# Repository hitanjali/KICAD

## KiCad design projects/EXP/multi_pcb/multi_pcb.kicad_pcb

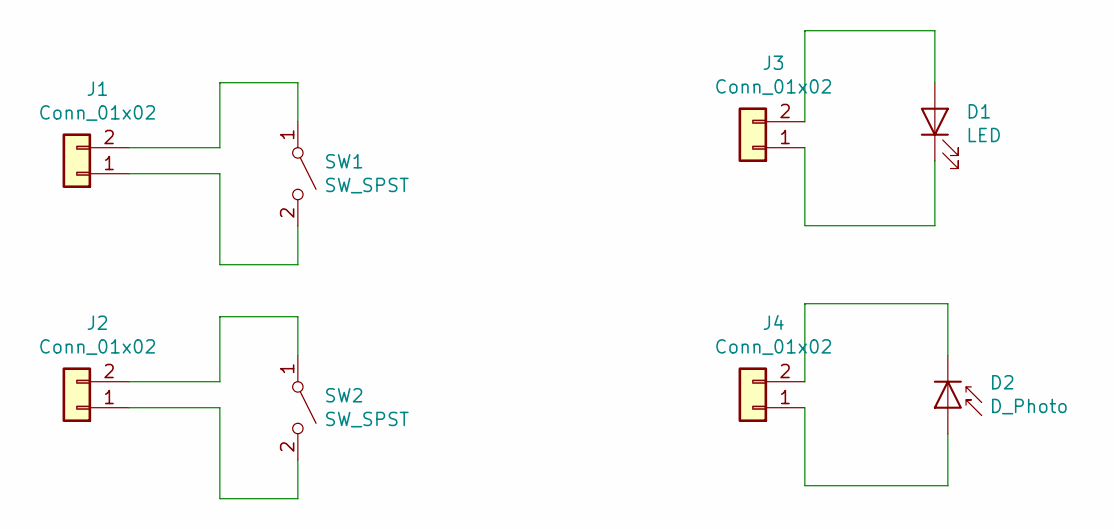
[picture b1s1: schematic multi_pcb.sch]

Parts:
D1: LED; LED_0805_2012Metric
D2: D_Photo; LED_0805_2012Metric
J1, J2, J3, J4: Conn_01x02; JST_EH_B02B-EH-A_1x02_P2.50mm_Vertical
SW1, SW2: SW_SPST; SW_DIP_SPSTx01_Slide_6.7x4.1mm_W6.73mm_P2.54mm_LowProfile_J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

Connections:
unnamed: D1.1 (K), J3.1
unnamed: D1.2 (A), J3.2
unnamed: D2.1 (K), J4.2
unnamed: D2.2 (A), J4.1
unnamed: J1.1, SW1.2 (B)
unnamed: J1.2, SW1.1 (A)
unnamed: J2.1, SW2.2 (B)
unnamed: J2.2, SW2.1 (A)

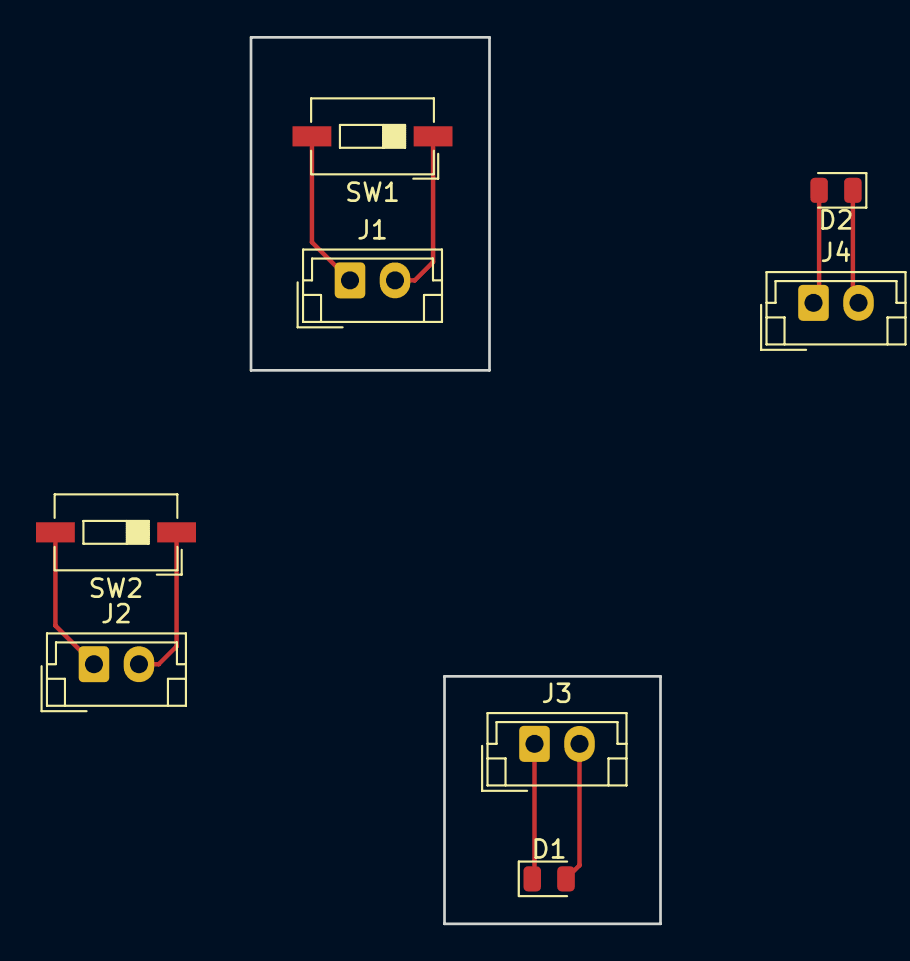
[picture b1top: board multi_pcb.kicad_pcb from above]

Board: 2 copper layers, 8 parts (0 on the bottom side), 8 nets.

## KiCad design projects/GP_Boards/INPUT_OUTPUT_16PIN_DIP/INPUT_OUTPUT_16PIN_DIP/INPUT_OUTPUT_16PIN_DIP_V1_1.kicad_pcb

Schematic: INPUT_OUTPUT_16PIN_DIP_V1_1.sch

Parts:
D1, D2, D3, D4, D5, D6, D7, D8, D9, D10, D11, D12, D13, D14, D15, D16, D17, D18, D19, D20, D21, D22, D23, D24, D25, D26, D27, D28, D29, D30, D31, D32: LED; LED_0603_1608Metric
J1, J2, J7, J8, J9, J12, J22, J28: Conn_01x04; PinHeader_1x04_P2.54mm_Vertical
J3, J6: Conn_01x01; PinHeader_1x01_P2.54mm_Vertical
J4, J5, J11, J24: Conn_02x04_Odd_Even; PinHeader_2x04_P2.54mm_Vertical
J10, J39: Conn_01x08; PinHeader_1x08_P2.54mm_Vertical
J13, J14, J15, J16, J17, J18, J19, J20, J25, J26, J31, J32, J33, J34, J35, J36, J37, J38: Conn_01x03; PinHeader_1x03_P2.54mm_Vertical
J21, J23, J29, J30: Conn_01x02; PinHeader_1x02_P2.54mm_Vertical
J27: Conn_02x08_Counter_Clockwise; DIP-16_W7.62mm
R1, R2, R3, R4, R5, R6, R7, R8, R9, R10, R11, R12, R13, R14, R15, R16, R25, R26, R27, R28, R29, R30, R31, R32, R33, R34, R35, R36, R37, R38, R39, R40: 150; R_1206_3216Metric
R17, R18, R19, R20, R21, R22, R23, R24, R41, R42, R43, R44, R45, R46, R47, R48: 10K; R_1206_3216Metric
RV1, RV2: 20K; Potentiometer_Bourns_3339P_Vertical
SW1, SW2: SW_DIP_x08; DIP-16_W7.62mm

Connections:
/1: J10.1, J13.2, J27.1
/2: J10.2, J14.2, J27.2
/3: J10.3, J15.2, J27.3
/4: J10.4, J16.2, J27.4
/5: J10.5, J17.2, J27.5
/6: J10.6, J18.2, J27.6
/7: J10.7, J19.2, J27.7
/8: J10.8, J20.2, J27.8
/9: J27.9, J31.2, J39.1
/10: J27.10, J32.2, J39.2
/11: J27.11, J33.2, J39.3
/12: J27.12, J34.2, J39.4
/13: J27.13, J35.2, J39.5
/14: J27.14, J36.2, J39.6
/15: J27.15, J37.2, J39.7
/16: J27.16, J38.2, J39.8
/I1: J13.3, R1.2, R17.2, SW1.16
/I2: J14.3, R2.2, R18.2, SW1.15
/I3: J15.3, R3.2, R19.2, SW1.14
/I4: J16.3, R4.2, R20.2, SW1.13
/I5: J17.3, R5.2, R21.2, SW1.12
/I6: J18.3, R6.2, R22.2, SW1.11
/I7: J19.3, R7.2, R23.2, SW1.10
/I8: J20.3, R8.2, R24.2, SW1.9
/I9: J31.1, R40.2, R48.2, SW2.8
/I10: J32.1, R39.2, R47.2, SW2.7
/I11: J33.1, R38.2, R46.2, SW2.6
/I12: J34.1, R37.2, R45.2, SW2.5
/I13: J35.1, R36.2, R44.2, SW2.4
/I14: J36.1, R35.2, R43.2, SW2.3
/I15: J37.1, R34.2, R42.2, SW2.2
/I16: J38.1, R33.2, R41.2, SW2.1
/O1: J13.1, R9.2
/O2: J14.1, R10.2
/O3: J15.1, R11.2
/O4: J16.1, R12.2
/O5: J17.1, R13.2
/O6: J18.1, R14.2
/O7: J19.1, R15.2
/O8: J20.1, R16.2
/O9: J31.3, R32.2
/O10: J32.3, R31.2
/O11: J33.3, R30.2
/O12: J34.3, R29.2
/O13: J35.3, R28.2
/O14: J36.3, R27.2
/O15: J37.3, R26.2
/O16: J38.3, R25.2
GNDREF: D1.1 (K), D2.1 (K), D3.1 (K), D4.1 (K), D5.1 (K), D6.1 (K), D7.1 (K), D8.1 (K), D9.1 (K), D10.1 (K), D11.1 (K), D12.1 (K), D13.1 (K), D14.1 (K), D15.1 (K), D16.1 (K), D17.1 (K), D18.1 (K), D19.1 (K), D20.1 (K), D21.1 (K), D22.1 (K), D23.1 (K), D24.1 (K), D25.1 (K), D26.1 (K), D27.1 (K), D28.1 (K), D29.1 (K), D30.1 (K), D31.1 (K), D32.1 (K), J26.2, R17.1, R18.1, R19.1, R20.1, R21.1, R22.1, R23.1, R24.1, R41.1, R42.1, R43.1, R44.1, R45.1, R46.1, R47.1, R48.1, RV1.3, RV2.1
unnamed: D1.2 (A), R1.1
unnamed: D2.2 (A), R2.1
unnamed: D3.2 (A), R3.1
unnamed: D4.2 (A), R4.1
unnamed: D5.2 (A), R5.1
unnamed: D6.2 (A), R6.1
unnamed: D7.2 (A), R7.1
unnamed: D8.2 (A), R8.1
unnamed: D9.2 (A), R9.1
unnamed: D10.2 (A), R10.1
unnamed: D11.2 (A), R11.1
unnamed: D12.2 (A), R12.1
unnamed: D13.2 (A), R13.1
unnamed: D14.2 (A), R14.1
unnamed: D15.2 (A), R15.1
unnamed: D16.2 (A), R16.1
unnamed: D17.2 (A), R25.1
unnamed: D18.2 (A), R26.1
unnamed: D19.2 (A), R27.1
unnamed: D20.2 (A), R28.1
unnamed: D21.2 (A), R29.1
unnamed: D22.2 (A), R30.1
unnamed: D23.2 (A), R31.1
unnamed: D24.2 (A), R32.1
unnamed: D25.2 (A), R33.1
unnamed: D26.2 (A), R34.1
unnamed: D27.2 (A), R35.1
unnamed: D28.2 (A), R36.1
unnamed: D29.2 (A), R37.1
unnamed: D30.2 (A), R38.1
unnamed: D31.2 (A), R39.1
unnamed: D32.2 (A), R40.1
unnamed: J1.1, J4.7
unnamed: J1.2, J4.5
unnamed: J1.3, J4.3
unnamed: J1.4, J4.1
unnamed: J2.1, J5.7
unnamed: J2.2, J5.5
unnamed: J2.3, J5.3
unnamed: J2.4, J5.1
unnamed: J3.1, RV1.2
unnamed: J4.2, J7.1
unnamed: J4.4, J7.2
unnamed: J4.6, J7.3
unnamed: J4.8, J7.4
unnamed: J5.2, J8.1
unnamed: J5.4, J8.2
unnamed: J5.6, J8.3
unnamed: J5.8, J8.4
unnamed: J6.1, RV2.2
unnamed: J9.4, J11.1
unnamed: J11.2, J12.1
unnamed: J9.3, J11.3
unnamed: J11.4, J12.2
unnamed: J9.2, J11.5
unnamed: J11.6, J12.3
unnamed: J9.1, J11.7
unnamed: J11.8, J12.4
unnamed: J21.1, J23.1, J26.1
unnamed: J21.2, J23.2, J25.3
unnamed: J22.1, J24.7
unnamed: J22.2, J24.5
unnamed: J22.3, J24.3
unnamed: J22.4, J24.1
unnamed: J24.2, J28.1
unnamed: J24.4, J28.2
unnamed: J24.6, J28.3
unnamed: J24.8, J28.4
unnamed: J25.1, J29.1, J30.1
unnamed: J26.3, J29.2, J30.2
VCC: J25.2, RV1.1, RV2.3, SW1.1, SW1.2, SW1.3, SW1.4, SW1.5, SW1.6, SW1.7, SW1.8, SW2.9, SW2.10, SW2.11, SW2.12, SW2.13, SW2.14, SW2.15, SW2.16

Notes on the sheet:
Version 1.1 : Added input feedback leds Added VCC and GND strips

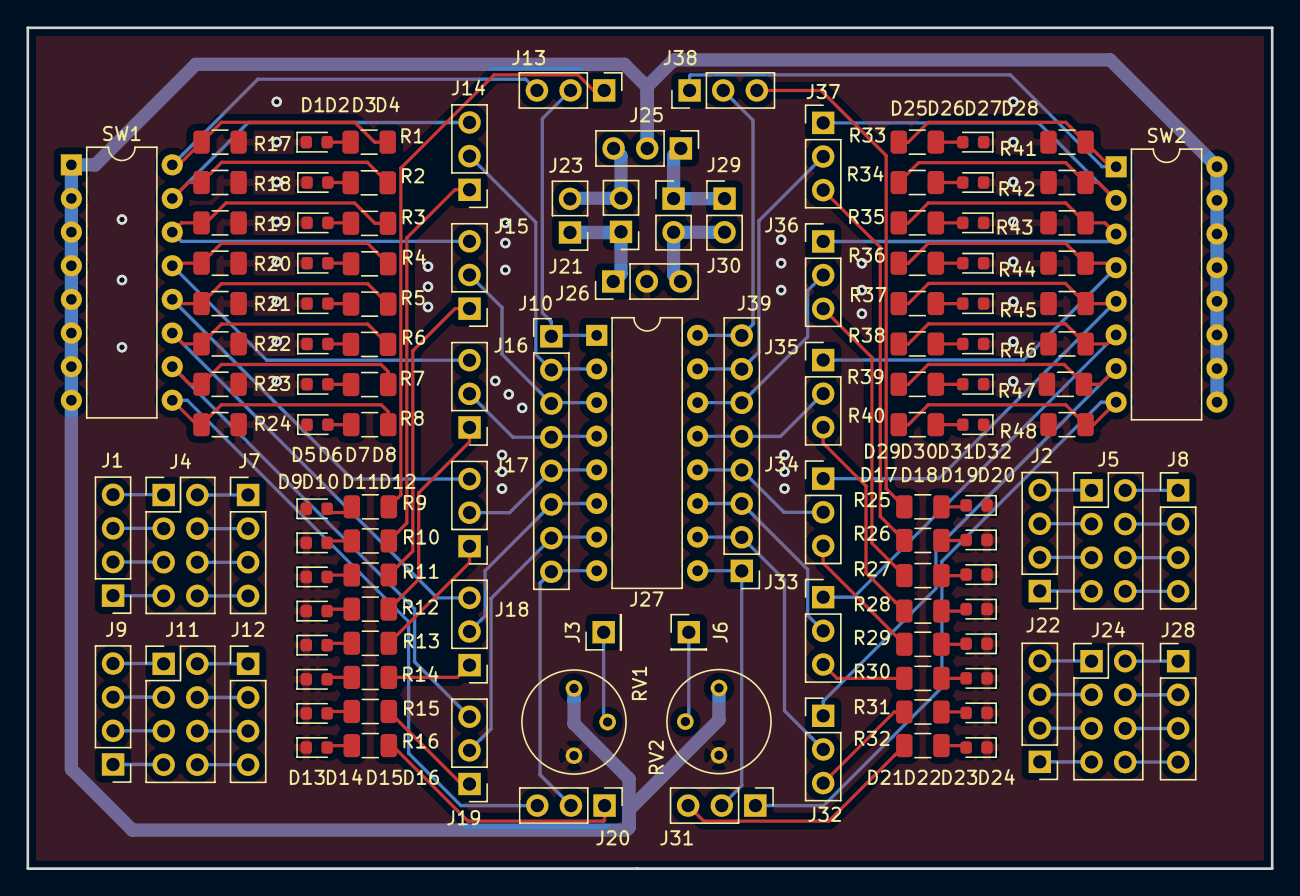
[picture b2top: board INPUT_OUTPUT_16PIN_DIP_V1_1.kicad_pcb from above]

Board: 2 copper layers, 94.0 x 63.5 mm, 123 parts (0 on the bottom side), 120 nets.

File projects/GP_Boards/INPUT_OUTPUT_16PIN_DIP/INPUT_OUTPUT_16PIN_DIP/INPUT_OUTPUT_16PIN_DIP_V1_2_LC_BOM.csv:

S.No,Manufacturing Part No,Designator,Quantity,Description(VALUE),Package(CASE),Top/Bottom,Points (No. of Pins),Comments,,
1,  , "D1, D2, D3, D4, D5, D6, D7, D8, D32, D31, D30, D29, D28, D27, D26, D25, " , "16" , "RED" , "LED_SMD:LED_0603_1608Metric" , TOP , 2, "Light emitting diode", , 
2,  , "D10, D11, D12, D13, D14, D15, D16, D9, D24, D23, D22, D21, D20, D19, D18, D17, " , "16" , "BLUE" , "LED_SMD:LED_0603_1608Metric" , TOP , 2, "Light emitting diode", , 
3,  , "J2, J4, J17, J19, " , "4" , "Conn_01x08" , "Connector_PinSocket_2.54mm:PinSocket_1x08_P2.54mm_Vertical" , TOP , 8, "Generic connector, single row, 01x08, script generated (kicad-library-utils/schlib/autogen/connector/)", , 
4,  , "J5, J3, " , "2" , "Conn_01x01" , "Connector_PinHeader_2.54mm:PinHeader_1x01_P2.54mm_Vertical" , TOP , 1, "Generic connector, single row, 01x01, script generated (kicad-library-utils/schlib/autogen/connector/)", , 
5,  , "J7, J35, J1, J6, J8, J21, " , "6" , "Conn_01x08" , "Connector_PinHeader_2.54mm:PinHeader_1x08_P2.54mm_Vertical" , TOP , 8, "Generic connector, single row, 01x08, script generated (kicad-library-utils/schlib/autogen/connector/)", , 
6,  , "J20, J18, J25, J26, " , "4" , "Conn_01x02" , "Connector_PinHeader_2.54mm:PinHeader_1x02_P2.54mm_Vertical" , TOP , 2, "Generic connector, single row, 01x02, script generated (kicad-library-utils/schlib/autogen/connector/)", , 
7,  , "J24, " , "1" , "Conn_02x08_Counter_Clockwise" , "Package_DIP:DIP-16_W7.62mm" , TOP , 16, "Generic connector, double row, 02x08, counter clockwise pin numbering scheme (similar to DIP packge numbering), script generated (kicad-library-utils/schlib/autogen/connector/)", , 
8,  , "J27, J28, J29, J30, J31, J32, J33, J34, J9, J10, J11, J12, J13, J14, J15, J16, J22, J23, " , "18" , "Conn_01x03" , "Connector_PinHeader_2.54mm:PinHeader_1x03_P2.54mm_Vertical" , TOP , 3, "Generic connector, single row, 01x03, script generated (kicad-library-utils/schlib/autogen/connector/)", , 
9,  , "J36, J37, " , "2" , "Conn_01x05" , "Connector_PinHeader_2.54mm:PinHeader_1x05_P2.54mm_Vertical" , TOP , 5, "Generic connector, single row, 01x05, script generated (kicad-library-utils/schlib/autogen/connector/)", , 
10,  , "R25, R26, R27, R28, R29, R30, R31, R32, R16, R15, R14, R13, R12, R11, R10, R9, R8, R7, R6, R5, R4, R3, R2, R1, R33, R34, R35, R36, R37, R38, R39, R40, " , "32" , "150" , "Resistor_SMD:R_1206_3216Metric" , TOP , 2, "Resistor, US symbol", , 
11,  , "R41, R42, R43, R44, R45, R46, R47, R48, R17, R18, R19, R20, R21, R22, R23, R24, " , "16" , "10K" , "Resistor_SMD:R_1206_3216Metric" , TOP , 2, "Resistor, US symbol", , 
12,  , "RV1, RV2, " , "2" , "20K" , "Potentiometer_THT:Potentiometer_Bourns_3339P_Vertical" , TOP , 3, "Trim-potentiometer, US symbol", , 
13,  , "SW2, SW1, " , "2" , "SW_DIP_x08" , "Package_DIP:DIP-16_W7.62mm" , TOP , 16, "8x DIP Switch, Single Pole Single Throw (SPST) switch, small symbol", ,

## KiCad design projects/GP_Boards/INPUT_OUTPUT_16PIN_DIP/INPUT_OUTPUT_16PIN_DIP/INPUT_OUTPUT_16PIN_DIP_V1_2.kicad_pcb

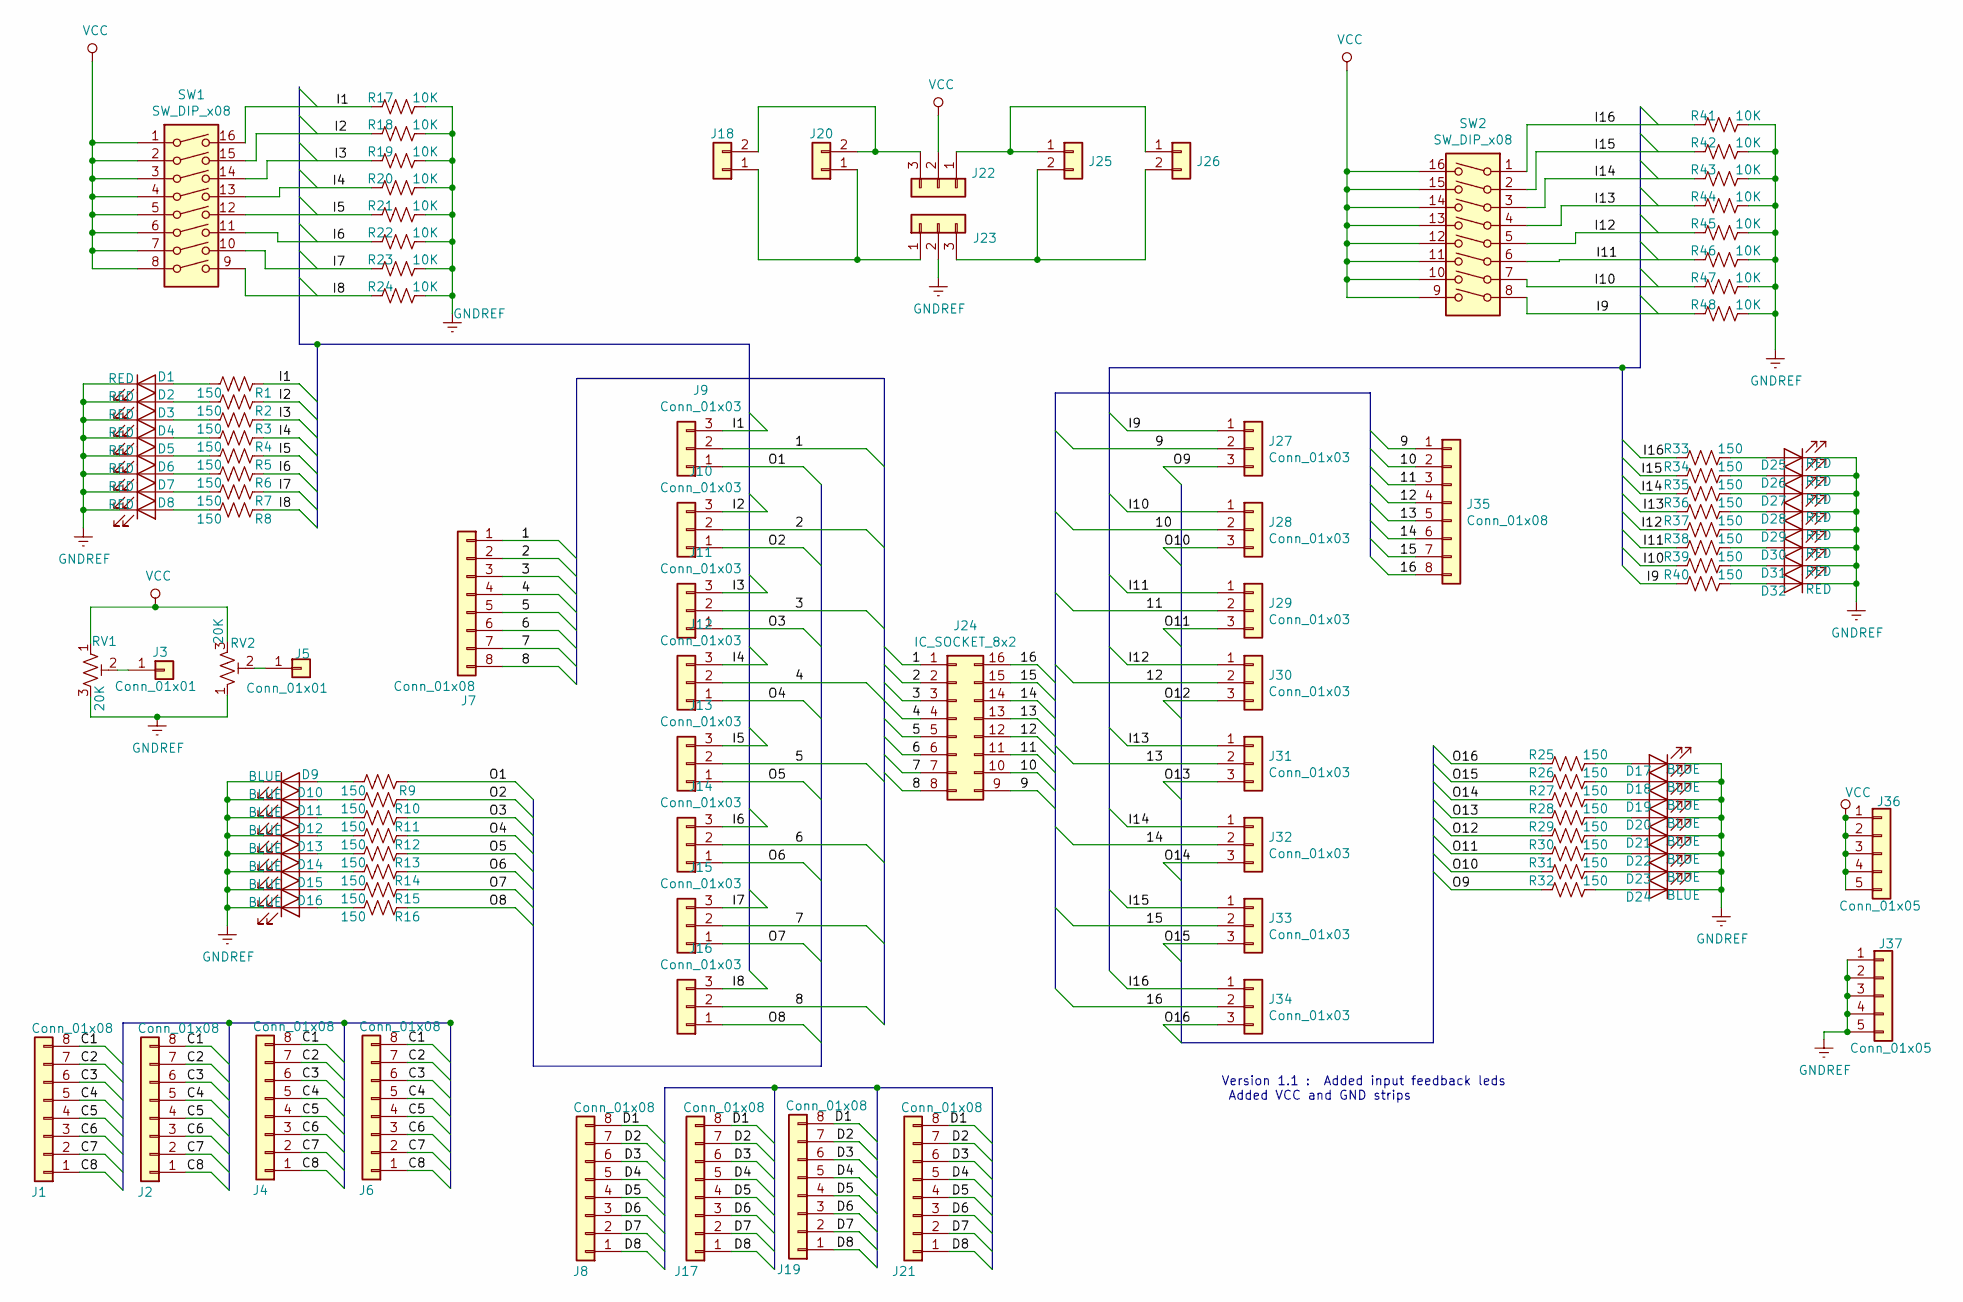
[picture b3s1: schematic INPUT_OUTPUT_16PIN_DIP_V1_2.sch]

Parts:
D1, D2, D3, D4, D5, D6, D7, D8, D25, D26, D27, D28, D29, D30, D31, D32: RED; LED_0603_1608Metric
D9, D10, D11, D12, D13, D14, D15, D16, D17, D18, D19, D20, D21, D22, D23, D24: BLUE; LED_0603_1608Metric
J1, J6, J7, J8, J21, J35: Conn_01x08; PinHeader_1x08_P2.54mm_Vertical
J2, J4, J17, J19: Conn_01x08; PinSocket_1x08_P2.54mm_Vertical
J3, J5: Conn_01x01; PinHeader_1x01_P2.54mm_Vertical
J9, J10, J11, J12, J13, J14, J15, J16, J22, J23, J27, J28, J29, J30, J31, J32, J33, J34: Conn_01x03; PinHeader_1x03_P2.54mm_Vertical
J18, J20, J25, J26: Conn_01x02; PinHeader_1x02_P2.54mm_Vertical
J24: IC_SOCKET_8x2; DIP-16_W7.62mm
J36, J37: Conn_01x05; PinHeader_1x05_P2.54mm_Vertical
R1, R2, R3, R4, R5, R6, R7, R8, R9, R10, R11, R12, R13, R14, R15, R16, R25, R26, R27, R28, R29, R30, R31, R32, R33, R34, R35, R36, R37, R38, R39, R40: 150; R_1206_3216Metric
R17, R18, R19, R20, R21, R22, R23, R24, R41, R42, R43, R44, R45, R46, R47, R48: 10K; R_1206_3216Metric
RV1, RV2: 20K; Potentiometer_Bourns_3339P_Vertical
SW1, SW2: SW_DIP_x08; DIP-16_W7.62mm

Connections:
/1: J7.1, J9.2, J24.1
/2: J7.2, J10.2, J24.2
/3: J7.3, J11.2, J24.3
/4: J7.4, J12.2, J24.4
/5: J7.5, J13.2, J24.5
/6: J7.6, J14.2, J24.6
/7: J7.7, J15.2, J24.7
/8: J7.8, J16.2, J24.8
/9: J24.9, J27.2, J35.1
/10: J24.10, J28.2, J35.2
/11: J24.11, J29.2, J35.3
/12: J24.12, J30.2, J35.4
/13: J24.13, J31.2, J35.5
/14: J24.14, J32.2, J35.6
/15: J24.15, J33.2, J35.7
/16: J24.16, J34.2, J35.8
/C1: J1.8, J2.8, J4.8, J6.8
/C2: J1.7, J2.7, J4.7, J6.7
/C3: J1.6, J2.6, J4.6, J6.6
/C4: J1.5, J2.5, J4.5, J6.5
/C5: J1.4, J2.4, J4.4, J6.4
/C6: J1.3, J2.3, J4.3, J6.3
/C7: J1.2, J2.2, J4.2, J6.2
/C8: J1.1, J2.1, J4.1, J6.1
/D1: J8.8, J17.8, J19.8, J21.8
/D2: J8.7, J17.7, J19.7, J21.7
/D3: J8.6, J17.6, J19.6, J21.6
/D4: J8.5, J17.5, J19.5, J21.5
/D5: J8.4, J17.4, J19.4, J21.4
/D6: J8.3, J17.3, J19.3, J21.3
/D7: J8.2, J17.2, J19.2, J21.2
/D8: J8.1, J17.1, J19.1, J21.1
/I1: J9.3, R1.2, R17.2, SW1.16
/I2: J10.3, R2.2, R18.2, SW1.15
/I3: J11.3, R3.2, R19.2, SW1.14
/I4: J12.3, R4.2, R20.2, SW1.13
/I5: J13.3, R5.2, R21.2, SW1.12
/I6: J14.3, R6.2, R22.2, SW1.11
/I7: J15.3, R7.2, R23.2, SW1.10
/I8: J16.3, R8.2, R24.2, SW1.9
/I9: J27.1, R40.2, R48.2, SW2.8
/I10: J28.1, R39.2, R47.2, SW2.7
/I11: J29.1, R38.2, R46.2, SW2.6
/I12: J30.1, R37.2, R45.2, SW2.5
/I13: J31.1, R36.2, R44.2, SW2.4
/I14: J32.1, R35.2, R43.2, SW2.3
/I15: J33.1, R34.2, R42.2, SW2.2
/I16: J34.1, R33.2, R41.2, SW2.1
/O1: J9.1, R9.2
/O2: J10.1, R10.2
/O3: J11.1, R11.2
/O4: J12.1, R12.2
/O5: J13.1, R13.2
/O6: J14.1, R14.2
/O7: J15.1, R15.2
/O8: J16.1, R16.2
/O9: J27.3, R32.2
/O10: J28.3, R31.2
/O11: J29.3, R30.2
/O12: J30.3, R29.2
/O13: J31.3, R28.2
/O14: J32.3, R27.2
/O15: J33.3, R26.2
/O16: J34.3, R25.2
GNDREF: D1.1 (K), D2.1 (K), D3.1 (K), D4.1 (K), D5.1 (K), D6.1 (K), D7.1 (K), D8.1 (K), D9.1 (K), D10.1 (K), D11.1 (K), D12.1 (K), D13.1 (K), D14.1 (K), D15.1 (K), D16.1 (K), D17.1 (K), D18.1 (K), D19.1 (K), D20.1 (K), D21.1 (K), D22.1 (K), D23.1 (K), D24.1 (K), D25.1 (K), D26.1 (K), D27.1 (K), D28.1 (K), D29.1 (K), D30.1 (K), D31.1 (K), D32.1 (K), J23.2, J37.1, J37.2, J37.3, J37.4, J37.5, R17.1, R18.1, R19.1, R20.1, R21.1, R22.1, R23.1, R24.1, R41.1, R42.1, R43.1, R44.1, R45.1, R46.1, R47.1, R48.1, RV1.3, RV2.1
unnamed: D1.2 (A), R1.1
unnamed: D2.2 (A), R2.1
unnamed: D3.2 (A), R3.1
unnamed: D4.2 (A), R4.1
unnamed: D5.2 (A), R5.1
unnamed: D6.2 (A), R6.1
unnamed: D7.2 (A), R7.1
unnamed: D8.2 (A), R8.1
unnamed: D9.2 (A), R9.1
unnamed: D10.2 (A), R10.1
unnamed: D11.2 (A), R11.1
unnamed: D12.2 (A), R12.1
unnamed: D13.2 (A), R13.1
unnamed: D14.2 (A), R14.1
unnamed: D15.2 (A), R15.1
unnamed: D16.2 (A), R16.1
unnamed: D17.2 (A), R25.1
unnamed: D18.2 (A), R26.1
unnamed: D19.2 (A), R27.1
unnamed: D20.2 (A), R28.1
unnamed: D21.2 (A), R29.1
unnamed: D22.2 (A), R30.1
unnamed: D23.2 (A), R31.1
unnamed: D24.2 (A), R32.1
unnamed: D25.2 (A), R33.1
unnamed: D26.2 (A), R34.1
unnamed: D27.2 (A), R35.1
unnamed: D28.2 (A), R36.1
unnamed: D29.2 (A), R37.1
unnamed: D30.2 (A), R38.1
unnamed: D31.2 (A), R39.1
unnamed: D32.2 (A), R40.1
unnamed: J3.1, RV1.2
unnamed: J5.1, RV2.2
unnamed: J18.1, J20.1, J23.1
unnamed: J18.2, J20.2, J22.3
unnamed: J22.1, J25.1, J26.1
unnamed: J23.3, J25.2, J26.2
VCC: J22.2, J36.1, J36.2, J36.3, J36.4, J36.5, RV1.1, RV2.3, SW1.1, SW1.2, SW1.3, SW1.4, SW1.5, SW1.6, SW1.7, SW1.8, SW2.9, SW2.10, SW2.11, SW2.12, SW2.13, SW2.14, SW2.15, SW2.16

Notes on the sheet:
Version 1.1 : Added input feedback leds Added VCC and GND strips

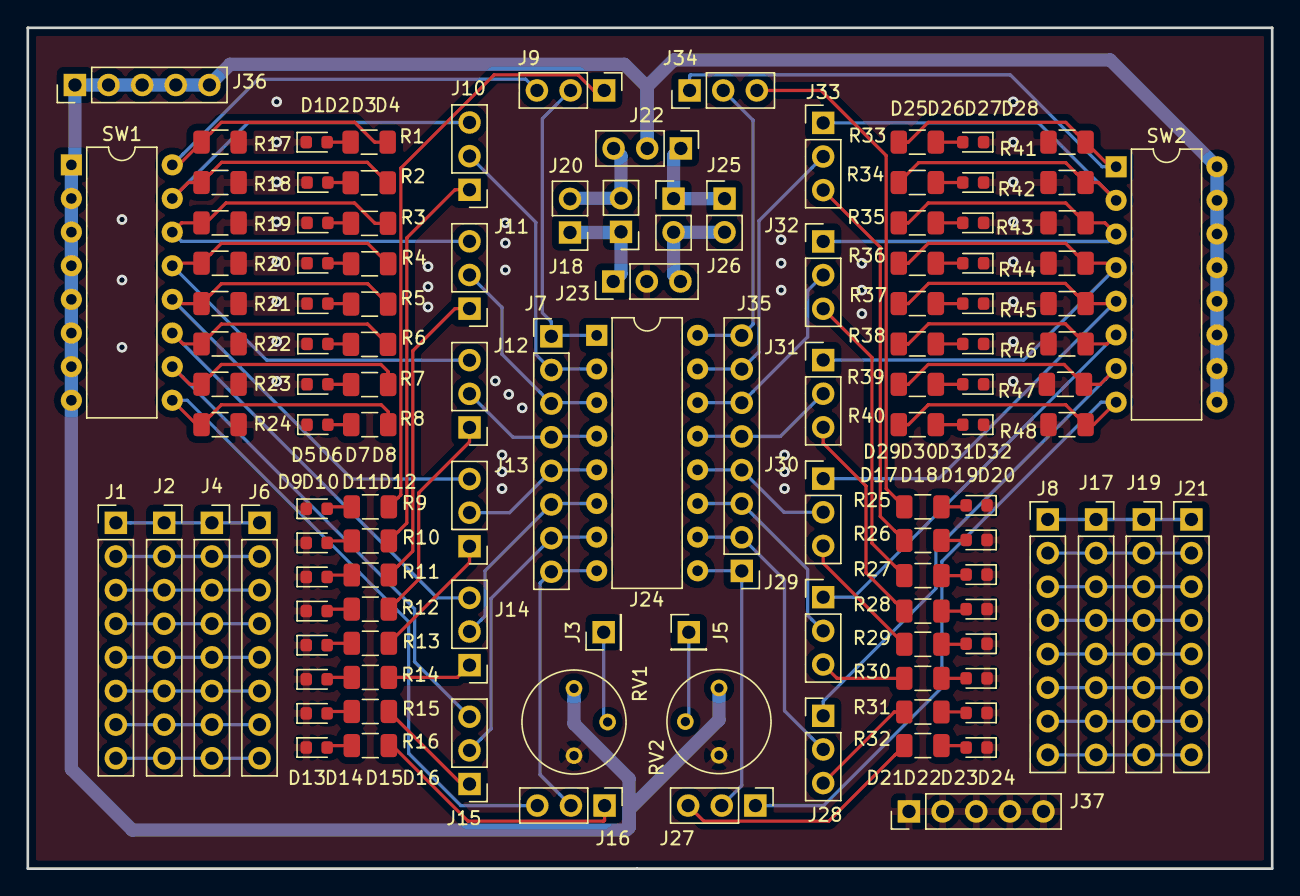
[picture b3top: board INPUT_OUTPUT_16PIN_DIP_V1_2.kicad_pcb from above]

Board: 2 copper layers, 94.0 x 63.5 mm, 121 parts (0 on the bottom side), 104 nets.

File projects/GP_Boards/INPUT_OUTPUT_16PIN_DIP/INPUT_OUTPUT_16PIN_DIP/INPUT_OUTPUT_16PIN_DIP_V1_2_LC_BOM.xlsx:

S.No | Manufacturing Part No | Designator | Quantity | Description(VALUE) | Package(CASE) | Top/Bottom | Points (No. of Pins) | Comments
1 |  | D1, D2, D3, D4, D5, D6, D7, D8, D32, D31, D30, D29, D28, D27, D26, D25, | 16 | RED | LED_SMD:LED_0603_1608Metric | TOP | 2 | Light emitting diode
2 |  | D10, D11, D12, D13, D14, D15, D16, D9, D24, D23, D22, D21, D20, D19, D18, D17, | 16 | BLUE | LED_SMD:LED_0603_1608Metric | TOP | 2 | Light emitting diode
3 |  | J2, J4, J17, J19, | 4 | Conn_01x08 | Connector_PinSocket_2.54mm:PinSocket_1x08_P2.54mm_Vertical | TOP | 8 | Generic connector, single row, 01x08, script generated (kicad-library-utils/sch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
4 |  | J5, J3, | 2 | Conn_01x01 | Connector_PinHeader_2.54mm:PinHeader_1x01_P2.54mm_Vertical | TOP | 1 | Generic connector, single row, 01x01, script generated (kicad-library-utils/sch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
5 |  | J7, J35, J1, J6, J8, J21, | 6 | Conn_01x08 | Connector_PinHeader_2.54mm:PinHeader_1x08_P2.54mm_Vertical | TOP | 8 | Generic connector, single row, 01x08, script generated (kicad-library-utils/sch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
6 |  | J20, J18, J25, J26, | 4 | Conn_01x02 | Connector_PinHeader_2.54mm:PinHeader_1x02_P2.54mm_Vertical | TOP | 2 | Generic connector, single row, 01x02, script generated (kicad-library-utils/sch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
7 |  | J24, | 1 | Conn_02x08_Counter_Clockwise | Package_DIP:DIP-16_W7.62mm | TOP | 16 | Generic connector, double row, 02x08, counter clockwise pin numbering scheme (s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
8 |  | J27, J28, J29, J30, J31, J32, J33, J34, J9, J10, J11, J12, J13, J14, J15, J16, 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 | 18 | Conn_01x03 | Connector_PinHeader_2.54mm:PinHeader_1x03_P2.54mm_Vertical | TOP | 3 | Generic connector, single row, 01x03, script generated (kicad-library-utils/sch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
9 |  | J36, J37, | 2 | Conn_01x05 | Connector_PinHeader_2.54mm:PinHeader_1x05_P2.54mm_Vertical | TOP | 5 | Generic connector, single row, 01x05, script generated (kicad-library-utils/sch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
10 |  | R25, R26, R27, R28, R29, R30, R31, R32, R16, R15, R14, R13, R12, R11, R10, R9, 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 | 32 | 150E | Resistor_SMD:R_1206_3216Metric | TOP | 2 | Resistor, US symbol
11 |  | R41, R42, R43, R44, R45, R46, R47, R48, R17, R18, R19, R20, R21, R22, R23, R24, | 16 | 10K | Resistor_SMD:R_1206_3216Metric | TOP | 2 | Resistor, US symbol
12 |  | RV1, RV2, | 2 | 20K | Potentiometer_THT:Potentiometer_Bourns_3339P_Vertical | TOP | 3 | Trim-potentiometer, US symbol
13 |  | SW2, SW1, | 2 | SW_DIP_x08 | Package_DIP:DIP-16_W7.62mm | TOP | 16 | 8x DIP Switch, Single Pole Single Throw (SPST) switch, small symbol

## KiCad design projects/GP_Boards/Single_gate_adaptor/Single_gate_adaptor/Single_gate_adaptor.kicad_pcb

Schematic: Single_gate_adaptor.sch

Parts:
D1, D2, D3, D4, D5, D6, D7, D8: RED_LED; LED_0603_1608Metric
J1, J3: Conn_01x15; PinHeader_1x15_P2.54mm_Vertical
J2, J4, J5: Conn_01x08; PinHeader_1x08_P2.54mm_Vertical
J6: Conn_01x03; PinHeader_1x03_P2.54mm_Vertical
R1, R2, R3, R4, R5, R6, R7, R8: 150E; R_0603_1608Metric
U1, U9: 74LVC1G97; SOT-23-6_Handsoldering
U2, U10: 74LVC1G98; SOT-23-6_Handsoldering
U3, U11: 74LVC1G04; SOT-23-5_HandSoldering
U4, U12: 74LVC1G14; SOT-23-5_HandSoldering
U5, U13: 74LVC1G17; SOT-23-5_HandSoldering
U6, U14: 74LVC1G125; SOT-23-5_HandSoldering
U7, U15: 74LVC1G86; SOT-23-5_HandSoldering
U8, U16: LMV321; SOT-23-5_HandSoldering

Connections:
/A1: J1.15, U3.2
/A2: J1.14, U4.2
/A3: J1.13, U5.2
/A4: J1.12, U6.2
/A5: J1.11, U6.1
/A6: J1.10, U7.2
/A7: J1.9, U7.1
/A8: J1.8, U1.3 (IN0)
/A9: J1.7, U1.1 (IN1)
/A10: J1.6, U1.6 (IN2)
/A11: J1.5, U2.3 (IN0)
/A12: J1.4, U2.1 (IN1)
/A13: J1.3, U2.6 (IN2)
/A14: J1.2, U8.3 (-)
/A15: J1.1, U8.1 (+)
/B1: J2.1, U3.4
/B2: J2.2, U4.4
/B3: J2.3, U5.4
/B4: J2.4, U6.4
/B5: J2.5, U7.4
/B6: J2.6, U1.4 (Y)
/B7: J2.7, U2.4 (~Y)
/B8: J2.8, U8.4
/C1: J3.15, U11.2
/C2: J3.14, U12.2
/C3: J3.13, U13.2
/C4: J3.12, U14.1
/C5: J3.11, U14.2
/C6: J3.10, U15.1
/C7: J3.9, U15.2
/C8: J3.8, U9.6 (IN2)
/C9: J3.7, U9.1 (IN1)
/C10: J3.6, U9.3 (IN0)
/C11: J3.5, U10.6 (IN2)
/C12: J3.4, U10.1 (IN1)
/C13: J3.3, U10.3 (IN0)
/C14: J3.2, U16.1 (+)
/C15: J3.1, U16.3 (-)
/D1: J4.1, U11.4
/D2: J4.2, U12.4
/D3: J4.3, U13.4
/D4: J4.4, U14.4
/D5: J4.5, U15.4
/D6: J4.6, U9.4 (Y)
/D7: J4.7, U10.4 (~Y)
/D8: J4.8, U16.4
GND: D1.1 (K), D2.1 (K), D3.1 (K), D4.1 (K), D5.1 (K), D6.1 (K), D7.1 (K), D8.1 (K), J6.3, U1.2 (GND), U2.2 (GND), U3.3 (GND), U4.3 (GND), U5.3 (GND), U6.3 (GND), U7.3 (GND), U8.2 (V-), U9.2 (GND), U10.2 (GND), U11.3 (GND), U12.3 (GND), U13.3 (GND), U14.3 (GND), U15.3 (GND), U16.2 (V-)
unnamed: D1.2 (A), R1.1
unnamed: D2.2 (A), R2.1
unnamed: D3.2 (A), R3.1
unnamed: D4.2 (A), R4.1
unnamed: D5.2 (A), R5.1
unnamed: D6.2 (A), R6.1
unnamed: D7.2 (A), R7.1
unnamed: D8.2 (A), R8.1
unnamed: J5.1, R8.2
unnamed: J5.2, R7.2
unnamed: J5.3, R6.2
unnamed: J5.4, R5.2
unnamed: J5.5, R4.2
unnamed: J5.6, R3.2
unnamed: J5.7, R2.2
unnamed: J5.8, R1.2
VCC: J6.2, U1.5 (VCC), U2.5 (VCC), U3.5 (VCC), U4.5 (VCC), U5.5 (VCC), U6.5 (VCC), U7.5 (VCC), U8.5 (V+), U9.5 (VCC), U10.5 (VCC), U11.5 (VCC), U12.5 (VCC), U13.5 (VCC), U14.5 (VCC), U15.5 (VCC), U16.5 (V+)

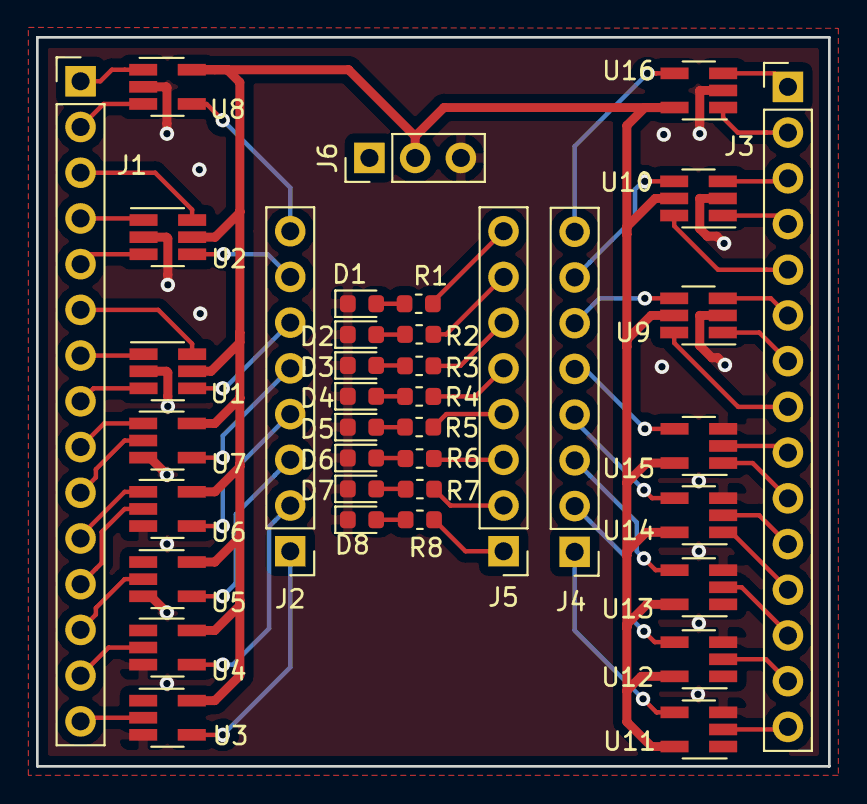
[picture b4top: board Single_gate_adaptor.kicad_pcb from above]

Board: 2 copper layers, 44.0 x 40.5 mm, 38 parts (0 on the bottom side), 64 nets.

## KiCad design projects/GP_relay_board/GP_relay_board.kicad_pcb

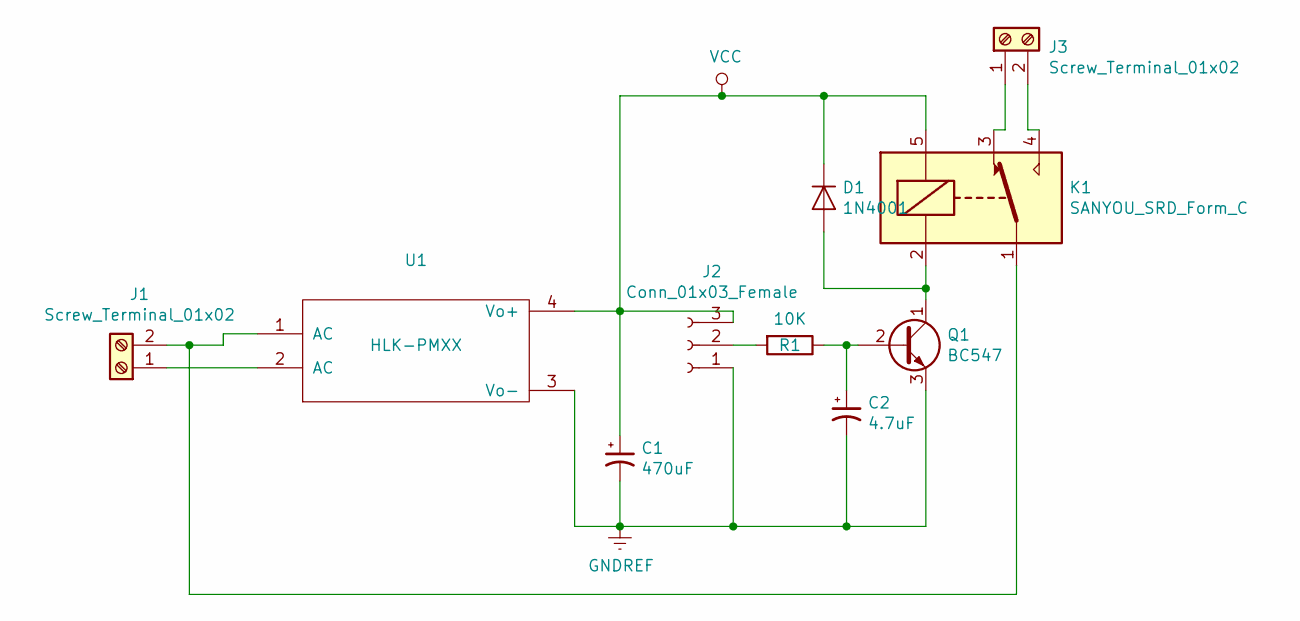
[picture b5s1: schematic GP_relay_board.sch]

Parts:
C1: 470uF; CP_Radial_D8.0mm_P3.50mm
C2: 4.7uF; CP_Radial_D4.0mm_P2.00mm
D1: 1N4001; D_DO-41_SOD81_P10.16mm_Horizontal
J1, J3: Screw_Terminal_01x02; TerminalBlock_bornier-2_P5.08mm
J2: Conn_01x03_Female; PinHeader_1x03_P2.54mm_Vertical
K1: SANYOU_SRD_Form_C; Relay_SPDT_SANYOU_SRD_Series_Form_C
Q1: BC547; TO-92_HandSolder
R1: 10K; R_Axial_DIN0207_L6.3mm_D2.5mm_P10.16mm_Horizontal
U1: HLK-PMXX

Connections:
GNDREF: C1.2, C2.2, J2.1, Q1.3 (E), U1.3 (Vo-)
unnamed: C2.1, Q1.2 (B), R1.1
unnamed: D1.2 (A), K1.2, Q1.1 (C)
unnamed: J1.1, U1.2 (AC)
unnamed: J1.2, K1.1, U1.1 (AC)
unnamed: J2.2, R1.2
unnamed: J3.1, K1.3
unnamed: J3.2, K1.4
VCC: C1.1, D1.1 (K), J2.3, K1.5, U1.4 (Vo+)

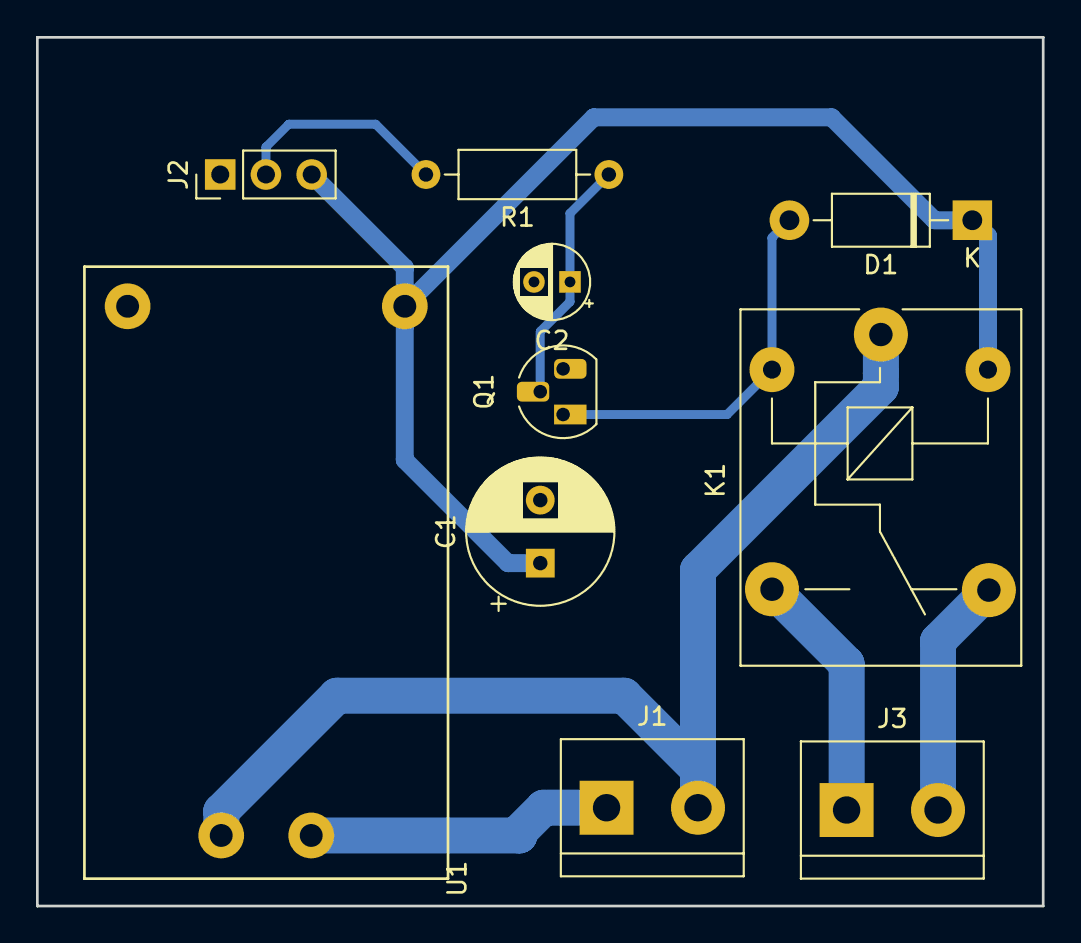
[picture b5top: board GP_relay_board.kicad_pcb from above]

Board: 2 copper layers, 55.9 x 48.3 mm, 10 parts (0 on the bottom side), 9 nets.
